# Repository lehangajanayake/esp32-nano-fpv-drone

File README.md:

# esp32-nano-fpv-drone
Im trying to create my own nano fpv drone based on esp32, and that can be controlled using you mobile phone

- System requirements, budget and BOM: [docs/requirements-budget-bom.md](docs/requirements-budget-bom.md)
- Shield PCB requirements (KiCad-ready): [hardware/shield/docs/shield-pcb-requirements.md](hardware/shield/docs/shield-pcb-requirements.md)

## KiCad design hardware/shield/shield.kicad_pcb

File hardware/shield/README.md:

# Shield PCB

The board the XIAO ESP32-S3 Sense plugs into (the XIAO sits on top, the shield's parts face down), carrying the four brushed motor drivers, the IMU, reverse polarity protection, battery sense and a status LED.

**Start here:** [docs/shield-pcb-requirements.md](docs/shield-pcb-requirements.md). It holds the outline, stackup, design rules, net classes, placement rules, the full net list and the BOM.

| File | Use |
| --- | --- |
| `docs/shield-pcb-requirements.md` | The requirements to build the schematic and layout from |
| `docs/kicad-build-steps.md` | Step-by-step brief for building the schematic and exporting a readable net list with the KiCad MCP |
| `bom/shield-bom.csv` | JLC-format BOM (Comment, Designator, Footprint, LCSC Part #) |
| `lib/symbols/`, `lib/footprints/`, `lib/3dmodels/` | Project-local libraries (XIAO, custom pads, STEP models) |
| `scripts/` | `gen_schematic.py` captured the first schematic from the requirements; `netlist_md.py` turns the exported net list into `exports/shield-netlist.md` and diffs it against section 5 |
| `exports/` | Schematic PDF and net list exported from KiCad, committed so they can be reviewed on GitHub |
| `production/` | Gerber, drill, BOM and CPL exports for an order (generated, not committed) |

## Creating the KiCad project

1. In KiCad, **File > New Project**, save it in this folder as `shield` (so you get `shield.kicad_pro`, `shield.kicad_sch`, `shield.kicad_pcb` here; untick "Create a new folder").
2. Add `lib/symbols/shield.kicad_sym` and `lib/footprints/shield.pretty` as **project** libraries using `${KIPRJMOD}` paths, so the project works from any clone.
3. Enter the design rules and net classes from sections 2.1 and 6.1 of the requirements in **Board Setup** before routing.
4. Check every item in section 11 of the requirements before freezing the schematic.

## Schematic status (v0.1, 2026-11-26)

`shield.kicad_sch` is captured and matches section 5 of the requirements pin for pin (see the check at the end of [exports/shield-netlist.md](exports/shield-netlist.md)). No PCB yet.

- **ERC: 0 errors, 1 warning, accepted.** `pin_to_pin`: U1 pin 2 (SDx, bidirectional) is on GND, which carries a PWR_FLAG (power output). SDx is tied to GND on purpose because the aux I2C master is unused (section 4.4), so the warning is expected.
- The first version was generated by `scripts/gen_schematic.py` against KiCad 10's standard libraries. From now on **edit `shield.kicad_sch` in KiCad**; re-running the script would overwrite manual edits.
- Project libraries: `shield:DMP2008UFG` (copy of KiCad's DMP3013SFV, same PowerDI3333-8 pinout), `shield:LSM6DS3TR-C` (copy of KiCad's LSM6DS3, same LGA-14 pinout), and footprints `shield:BAT_Pads_3x3.5mm` and `shield:Motor_Pads_2x2mm` from sections 4.1 and 4.2.
- NT1 uses KiCad's `NetTie:NetTie-2_SMD_Pad2.0mm` (the closest stock net tie to the 1.5 mm in section 6.2).
- The sheet is A3 rather than A4 so the labels stay readable.
- J1, J2, BAT1, MOT1 to MOT4, NT1, TP1 to TP5 are excluded from the BOM and position files; every assembled part has an `LCSC` field.

Regenerate the exports after any schematic change (from this folder):

```sh
kicad-cli sch erc -o exports/shield-erc.rpt shield.kicad_sch
kicad-cli sch export pdf -o exports/shield-schematic.pdf shield.kicad_sch
kicad-cli sch export netlist --format kicadxml -o exports/shield.net.xml shield.kicad_sch
kicad-cli sch export bom --fields 'Reference,Value,Footprint,LCSC,${QUANTITY}' --group-by 'Value,Footprint,LCSC' -o exports/shield-bom.csv shield.kicad_sch
python3 scripts/netlist_md.py
```

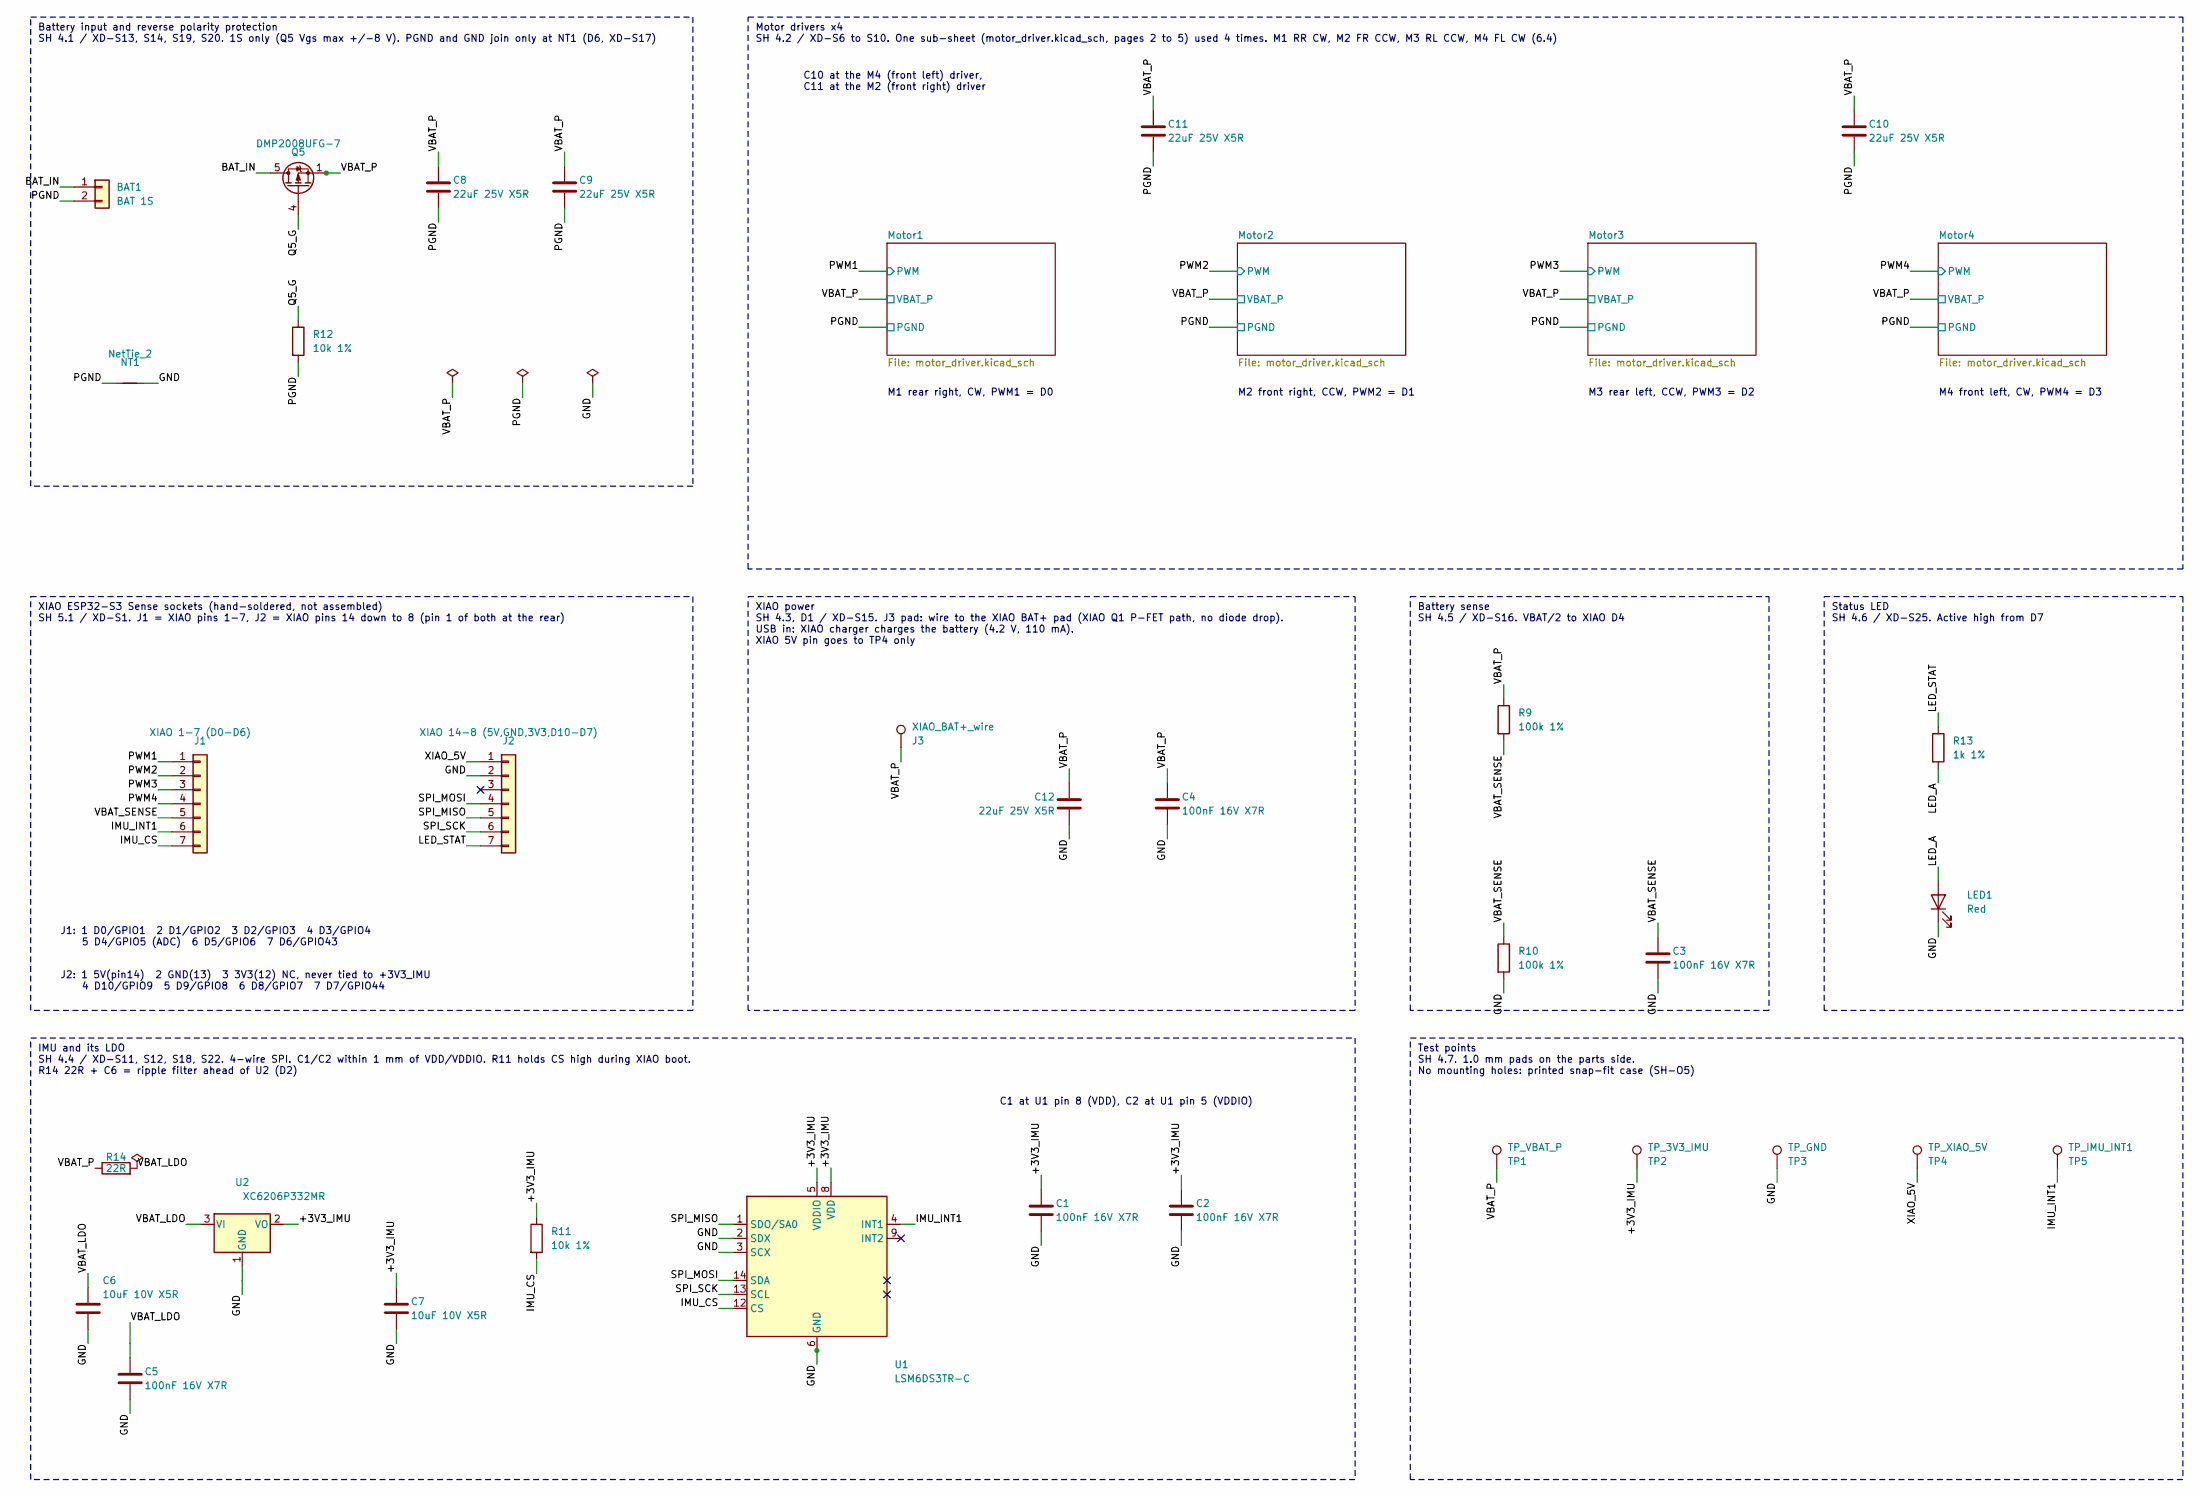
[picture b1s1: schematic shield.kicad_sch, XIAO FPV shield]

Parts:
BAT1: BAT 1S; BAT_Pads_3x3.5mm
C1, C2, C3, C4, C5: 100nF 16V X7R; C_0402_1005Metric; LCSC C1525
C6, C7: 10uF 10V X5R; C_0603_1608Metric; LCSC C19702
C8, C9, C10, C11, C12: 22uF 25V X5R; C_0805_2012Metric; LCSC C45783
J1: XIAO 1-7 (D0-D6); PinSocket_1x07_P2.54mm_Vertical
J2: XIAO 14-8 (5V,GND,3V3,D10-D7); PinSocket_1x07_P2.54mm_Vertical
J3: XIAO_BAT+_wire; TestPoint_THTPad_2.0x2.0mm_Drill1.0mm
LED1: Red; LED_0603_1608Metric; LCSC C2286
NT1: NetTie_2; NetTie-2_SMD_Pad2.0mm
Q5: DMP2008UFG-7; Diodes_PowerDI3333-8; LCSC C461052
R9, R10: 100k 1%; R_0402_1005Metric; LCSC C25741
R11, R12: 10k 1%; R_0402_1005Metric; LCSC C25744
R13: 1k 1%; R_0402_1005Metric; LCSC C11702
R14: 22R; R_0402_1005Metric; LCSC C25092
TP1: TP_VBAT_P; TestPoint_Pad_D1.0mm
TP2: TP_3V3_IMU; TestPoint_Pad_D1.0mm
TP3: TP_GND; TestPoint_Pad_D1.0mm
TP4: TP_XIAO_5V; TestPoint_Pad_D1.0mm
TP5: TP_IMU_INT1; TestPoint_Pad_D1.0mm
U1: LSM6DS3TR-C; LGA-14_3x2.5mm_P0.5mm_LayoutBorder3x4y; LCSC C967633
U2: XC6206P332MR; SOT-23-3; LCSC C5446

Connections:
/+3V3_IMU: C1.1, C2.1, C7.1, R11.1, TP2.1, U1.5 (VDDIO), U1.8 (VDD), U2.2 (VO)
/BAT_IN: BAT1.1, Q5.5 (D)
/GND: C1.2, C2.2, C3.2, C4.2, C5.2, C6.2, C7.2, C12.2, J2.2, LED1.1 (K), NT1.2, R10.2, TP3.1, U1.2 (SDX), U1.3 (SCX), U1.6 (GND), U1.7 (GND), U2.1 (GND)
/IMU_CS: J1.7, R11.2, U1.12 (CS)
/IMU_INT1: J1.6, TP5.1, U1.4 (INT1)
/LED_A: LED1.2 (A), R13.2
/LED_STAT: J2.7, R13.1
/PGND: BAT1.2, C8.2, C9.2, C10.2, C11.2, NT1.1, R12.2; also elsewhere on the board
/PWM1: J1.1; also elsewhere on the board
/PWM2: J1.2; also elsewhere on the board
/PWM3: J1.3; also elsewhere on the board
/PWM4: J1.4; also elsewhere on the board
/Q5_G: Q5.4 (G), R12.1
/SPI_MISO: J2.5, U1.1 (SDO/SA0)
/SPI_MOSI: J2.4, U1.14 (SDA)
/SPI_SCK: J2.6, U1.13 (SCL)
/VBAT_LDO: C5.1, C6.1, R14.2, U2.3 (VI)
/VBAT_P: C4.1, C8.1, C9.1, C10.1, C11.1, C12.1, J3.1, Q5.1 (S), Q5.2 (S), Q5.3 (S), R9.1, R14.1, TP1.1; also elsewhere on the board
/VBAT_SENSE: C3.1, J1.5, R9.2, R10.1
/XIAO_5V: J2.1, TP4.1

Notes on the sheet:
Battery input and reverse polarity protection SH 4.1 / XD-S13, S14, S19, S20. 1S only (Q5 Vgs max +/-8 V). PGND and GND join only at NT1 (D6, XD-S17)
Motor drivers x4 SH 4.2 / XD-S6 to S10. One sub-sheet (motor_driver.kicad_sch, pages 2 to 5) used 4 times. M1 RR CW, M2 FR CCW, M3 RL CCW, M4 FL CW (6.4)
XIAO ESP32-S3 Sense sockets (hand-soldered, not assembled) SH 5.1 / XD-S1. J1 = XIAO pins 1-7, J2 = XIAO pins 14 down to 8 (pin 1 of both at the rear)
XIAO power SH 4.3, D1 / XD-S15. J3 pad: wire to the XIAO BAT+ pad (XIAO Q1 P-FET path, no diode drop). USB in: XIAO charger charges the battery (4.2 V, 110 mA). XIAO 5V pin goes to TP4 only
IMU and its LDO SH 4.4 / XD-S11, S12, S18, S22. 4-wire SPI. C1/C2 within 1 mm of VDD/VDDIO. R11 holds CS high during XIAO boot. R14 22R + C6 = ripple filter ahead of U2 (D2)
Battery sense SH 4.5 / XD-S16. VBAT/2 to XIAO D4
Status LED SH 4.6 / XD-S25. Active high from D7
Test points SH 4.7. 1.0 mm pads on the parts side. No mounting holes: printed snap-fit case (SH-O5)
C10 at the M4 (front left) driver, C11 at the M2 (front right) driver
J1: 1 D0/GPIO1 2 D1/GPIO2 3 D2/GPIO3 4 D3/GPIO4 5 D4/GPIO5 (ADC) 6 D5/GPIO6 7 D6/GPIO43
J2: 1 5V(pin14) 2 GND(13) 3 3V3(12) NC, never tied to +3V3_IMU 4 D10/GPIO9 5 D9/GPIO8 6 D8/GPIO7 7 D7/GPIO44
C1 at U1 pin 8 (VDD), C2 at U1 pin 5 (VDDIO)
M1 rear right, CW, PWM1 = D0
M2 front right, CCW, PWM2 = D1
M3 rear left, CCW, PWM3 = D2
M4 front left, CW, PWM4 = D3

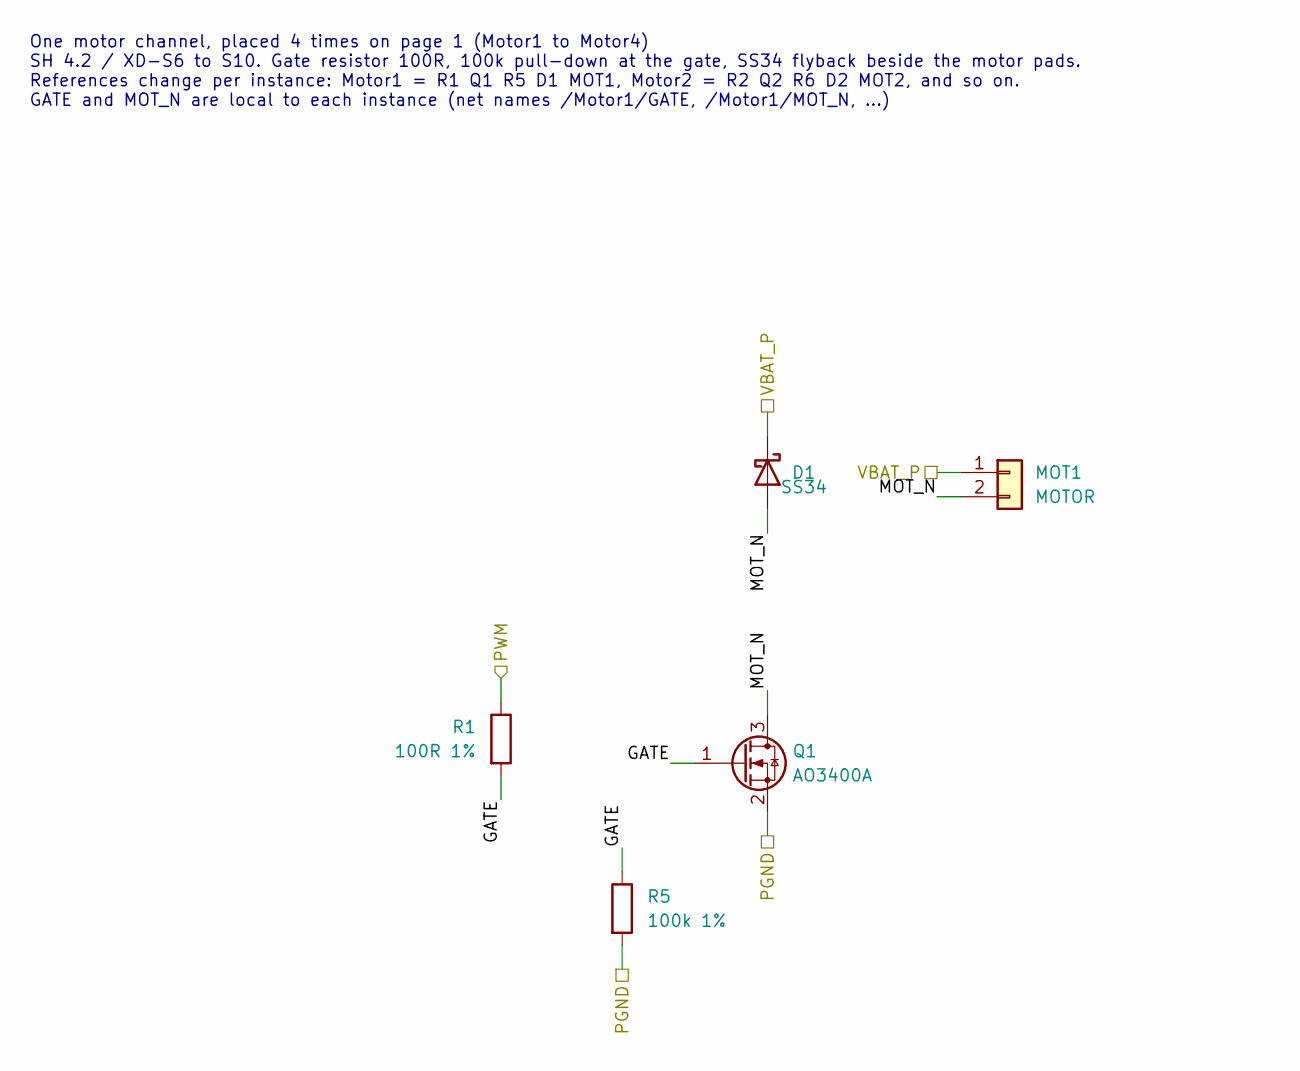
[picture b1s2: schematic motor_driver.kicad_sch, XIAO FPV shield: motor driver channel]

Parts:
D1: SS34; D_SMA; LCSC C8678
MOT1: MOTOR; Motor_Pads_2x2mm
Q1: AO3400A; SOT-23; LCSC C20917
R1: 100R 1%; R_0402_1005Metric; LCSC C25076
R5: 100k 1%; R_0402_1005Metric; LCSC C25741

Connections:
/Motor1/GATE: Q1.1 (G), R1.2, R5.1
/Motor1/MOT_N: D1.2 (A), MOT1.2, Q1.3 (D)
/PGND: Q1.2 (S), R5.2; also elsewhere on the board
/PWM1: R1.1; also elsewhere on the board
/VBAT_P: D1.1 (K), MOT1.1; also elsewhere on the board

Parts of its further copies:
D2, D3, D4: SS34; D_SMA; LCSC C8678
MOT2, MOT3, MOT4: MOTOR; Motor_Pads_2x2mm
Q2, Q3, Q4: AO3400A; SOT-23; LCSC C20917
R2, R3, R4: 100R 1%; R_0402_1005Metric; LCSC C25076
R6, R7, R8: 100k 1%; R_0402_1005Metric; LCSC C25741

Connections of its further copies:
/Motor2/GATE: Q2.1 (G), R2.2, R6.1
/Motor2/MOT_N: D2.2 (A), MOT2.2, Q2.3 (D)
/Motor3/GATE: Q3.1 (G), R3.2, R7.1
/Motor3/MOT_N: D3.2 (A), MOT3.2, Q3.3 (D)
/Motor4/GATE: Q4.1 (G), R4.2, R8.1
/Motor4/MOT_N: D4.2 (A), MOT4.2, Q4.3 (D)
/PGND: Q2.2 (S), Q3.2 (S), Q4.2 (S), R6.2, R7.2, R8.2; also elsewhere on the board
/PWM2: R2.1; also elsewhere on the board
/PWM3: R3.1; also elsewhere on the board
/PWM4: R4.1; also elsewhere on the board
/VBAT_P: D2.1 (K), D3.1 (K), D4.1 (K), MOT2.1, MOT3.1, MOT4.1; also elsewhere on the board

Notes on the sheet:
One motor channel, placed 4 times on page 1 (Motor1 to Motor4) SH 4.2 / XD-S6 to S10. Gate resistor 100R, 100k pull-down at the gate, SS34 flyback beside the motor pads. References change per instance: Motor1 = R1 Q1 R5 D1 MOT1, Motor2 = R2 Q2 R6 D2 MOT2, and so on. GATE and MOT_N are local to each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

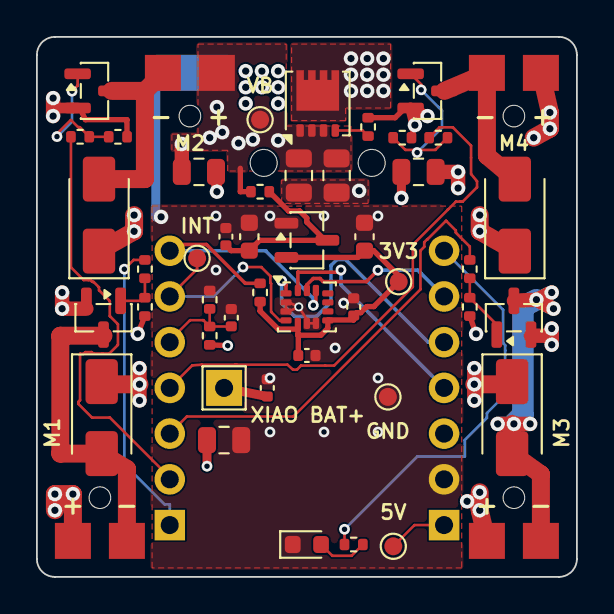
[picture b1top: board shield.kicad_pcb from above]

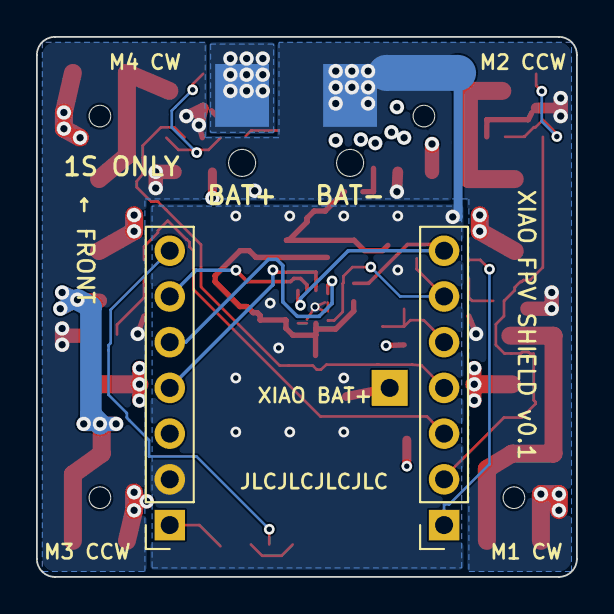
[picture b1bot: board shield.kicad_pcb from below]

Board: 4 copper layers, 30.0 x 30.0 mm, 52 parts (4 on the bottom side), 28 nets.

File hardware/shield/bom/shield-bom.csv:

Comment,Designator,Footprint,LCSC Part #,Type,Note
LSM6DS3TR-C,U1,LGA-14_2.5x3mm_P0.5mm,C967633,Extended,
XC6206P332MR-G,U2,SOT-23,C5446,Basic,
AO3400A,"Q1,Q2,Q3,Q4",SOT-23,C20917,Basic,
DMP2008UFG-7,Q5,PowerDI3333-8,C461052,Extended,
SS34,"D1,D2,D3,D4",D_SMA,C8678,Basic,
100R 1%,"R1,R2,R3,R4",R_0402_1005Metric,C25076,Basic,
100k 1%,"R5,R6,R7,R8,R9,R10",R_0402_1005Metric,C25741,Basic,
10k 1%,"R11,R12",R_0402_1005Metric,C25744,Basic,
1k 1%,R13,R_0402_1005Metric,C11702,Basic,
22R 1%,R14,R_0402_1005Metric,C25092,Basic,IMU LDO ripple filter + isolation link
100nF 16V X7R,"C1,C2,C3,C4,C5",C_0402_1005Metric,C1525,Basic,
10uF 10V X5R,"C6,C7",C_0603_1608Metric,C19702,Basic,
22uF 25V X5R,"C8,C9,C10,C11,C12",C_0805_2012Metric,C45783,Basic,
Red LED KT-0603R,LED1,LED_0603_1608Metric,C2286,Basic,
